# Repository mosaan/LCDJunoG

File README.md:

Roland Juno G LCD Emulator
==========================

LCD replacement project for Roland Juno G.
The original source is [dpeddi's work](https://github.com/dpeddi/LCDJunoG) under BSD-3-Clause license.
```
 * Copyright (c) 2022 Eddi De Pieri
 * Most code borrowed by Pico-DMX by Jostein Løwer 
 * Modified for performance by bjaan
```

Slight modifications as follows
- (WIP) LCD now uses 8-bit parallel mode for better refresh rate.
- Pin definitions in `platformio.ini` now work correctly. See `platformio.ini` for pinout notes.
- Fix few minor bugs.
- Refactor codes for better readability.
- Remove `MODE_BRIGHTNESS` and change functionality of `MODE_BGCOLOR`. (see below)

About `MODE_BGCOLOR`
====================

In `MODE_BGCOLOR`, you can control LCD background color with `LCD CONTRAST` knob on Juno G.

- In the first 3/4 of the knob, a color is selected from the hue ring according to the knob position.
- In the remaining 1/4 of the knob, the background color is fixed at white.

Without `MODE_BGCOLOR`, background color fixed to white.

PlatformIO Build Environments
=============================

There are 2 environments defined:
- `env:pico`: LCD runs in SPI mode.
- `env:pico-parallel`: LCD runs in 8bit parallel mode.

Althogh predefined pin assignments are carefully selected to make PCB creation easier,
you can choose other pins to match your needs.

BOM:
====

- Raspberry Pi Pico
- Display ILI9488 4.0” (purchased from [AliExpress](https://ja.aliexpress.com/item/1005003033844928.html))
- 1.0mm pitch 18-pin flexible flat cable. Length: 210mm (shorter might work), contacts on same side.
- FFC/FPC connector
  - 1.0mm pitch 18-pin, bottom connection; for Juno G connection.
  - (Needed in parallel mode only) 0.5mm pitch 40-pin, top connection; for LCD connection.
- 5 to 10 ohm reistor; for backlight LED on LCD.
- (Optional) 0.1uF ceramic capacitor; for "LCD CONTRAST" knob stability.

Predefined Pin Assignments (Parallel mode):
===========================================

| JunoG Pin | JunoG Function | RpiPico Pin |
| --------- | -------------- | ----------- |
| 18        | +5V            | VSYS        |
| 17        | GND            | GND         |
| 16        | +3V            | (Not used)  |
| 15        | RST            | GP21        |
| 14        | CS2 (*1)       | GP20        |
| 13        | CS1 (*1)       | GP19        |
| 12        | RS             | GP18        |
| 11        | WE             | GP17        |
| 10        | D0             | GP8         |
| 9         | D1             | GP9         |
| 8         | D2             | GP10        |
| 7         | D3             | GP11        |
| 6         | D4             | GP12        |
| 5         | D5             | GP13        |
| 4         | D6             | GP14        |
| 3         | D7             | GP15        |
| 2         | BRGT           | GP28        |
| 1         | BRGT Vref      | +3V         |

*1: Check if the pin configuration might be reversed

| LCD Pin# | LCD Function  | RpiPico Pin         |
| -------- | ------------- | ------------------- |
| 40       | IM2           | GND                 |
| 39       | IM1           | 3.3V                |
| 38       | IM0           | 3.3V                |
| 37       | GND           | GND                 |
| 36       | LED-K         | GND                 |
| 35       | LED-K         | GND                 |
| 34       | LED-K         | GND                 |
| 33       | LED-A         | (3.3V via resistor) |
| 32       | DB15          | (not used)          |
| 31       | DB14          | (not used)          |
| 30       | DB13          | (not used)          |
| 29       | DB12          | (not used)          |
| 28       | DB11          | (not used)          |
| 27       | DB10          | (not used)          |
| 26       | DB9           | (not used)          |
| 25       | DB8           | (not used)          |
| 24       | DB7           | GP7                 |
| 23       | DB6           | GP6                 |
| 22       | DB5           | GP5                 |
| 21       | DB4           | GP4                 |
| 20       | DB3           | GP3                 |
| 19       | DB2           | GP2                 |
| 18       | DB1           | GP1                 |
| 17       | DB0           | GP0                 |
| 16       | GND           | GND                 |
| 15       | RESET         | GP22                |
| 14       | SPI SDO       | (not used)          |
| 13       | SPI SDI/SDA   | (not used)          |
| 12       | RDX           | 3.3V                |
| 11       | WRX/SPI SCL   | GP26                |
| 10       | DCX/RS(SPI-4) | GP27                |
| 9        | CSX/SPI CS    | GND                 |
| 8        | FMARK(TE)     | (not used)          |
| 7        | VDDA          | 3.3V                |
| 6        | VDDI          | 3.3V                |
| 5        | GND           | GND                 |
| 4        | YD            | (not used)          |
| 3        | XR            | (not used)          |
| 2        | YU            | (not used)          |
| 1        | XL            | (not used)          |

Predefined Pin Assignments (SPI mode):
======================================

| JunoG Pin | JunoG Function | RpiPico Pin |
| --------- | -------------- | ----------- |
| 18        | +5V            | VSYS        |
| 17        | GND            | GND         |
| 16        | +3V            | (Not used)  |
| 15        | RST            | GP14        |
| 14        | CS1            | GP12        |
| 13        | CS2            | GP13        |
| 12        | RS             | GP11        |
| 11        | WE             | GP10        |
| 10        | D0             | GP2         |
| 9         | D1             | GP3         |
| 8         | D2             | GP4         |
| 7         | D3             | GP5         |
| 6         | D4             | GP6         |
| 5         | D5             | GP7         |
| 4         | D6             | GP8         |
| 3         | D7             | GP9         |
| 2         | BRGT           | GP26        |
| 1         | BRGT Vref      | +3V         |

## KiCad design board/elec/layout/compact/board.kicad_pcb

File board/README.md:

# Reference board design

This directory contains [atopile](https://atopile.io/) & [KiCad](https://www.kicad.org/) project files for the reference board design.

If you just need PCB gerber files, see `elec/layout/default/production/board.zip`.

## Folder & File structure

- `ato.yaml`: atopile project setting file. see [atopile documentation](https://atopile.io/config/).
- `elec/`: main project files related with atopile and KiCad
  - `footprints/`: KiCad footprints & 3D shape datas.
  - `layout/`: KiCad project files.
  - `src/`: atopile module files.

## To modify & build your own gerber files

1. Modify `elec/src/board.ato` as you like.
2. [Install atopile](https://atopile.io/getting-started/) and run `ato install & ato build` in this folder, then you got netlist file at `build/default.net`.
3. Open `elec/layout/board.kicad_pro` in KiCad and open PCB file (or just open `elec/layout/board.kicad_pcb`).
4. From `File` menu, select `Import -> Netlist...`, then select the generated netlist file.
5. Now netlist updated as you write in `elec/src/board.ato`. Change board layout as you like!

Subsequent steps is the same as the usual board design in KiCad. Refer to  KiCad documentation.

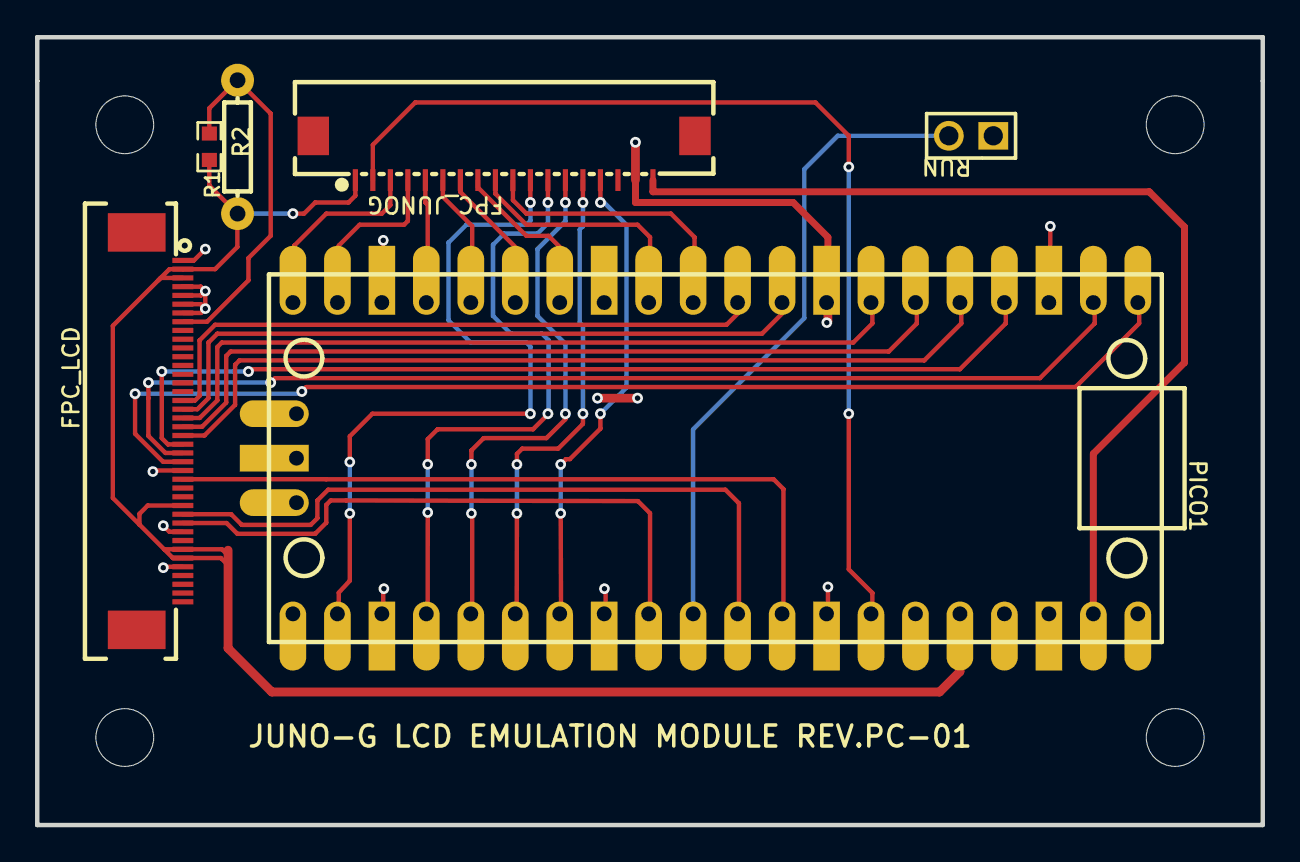
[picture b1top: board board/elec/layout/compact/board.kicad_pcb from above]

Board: 2 copper layers, 70.0 x 45.0 mm, 10 parts (0 on the bottom side), 30 nets.

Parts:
FPC_JUNOG: 1.0K-DX-18PWB; FPC-SMD_18P-P1.00_HDGC_1.0K-DX-18PWB
FPC_LCD: AFC07-S40ECA-00; FPC-SMD_P0.50-40P_LCS-SJ-H2.0
Hole_gge3520: Hole_gge3520
Hole_gge3523: Hole_gge3523
Hole_gge3526: Hole_gge3526
Hole_gge3529: Hole_gge3529
PICO1: RASPBERRY-PI-PICO_TH/SMT (No Debug Pins); RASPBERRY-PI-PICO
R1: 5R1; R0603
R2: 5R1; R_AXIAL-0.3
RUN: HDR-M-2.54_1x2; HDR-M-2.54_1X2

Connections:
3.3V: FPC_JUNOG.1, FPC_LCD.2, FPC_LCD.3, FPC_LCD.29, FPC_LCD.34, FPC_LCD.35, PICO1.36, R1.1, R2.1
+5V: FPC_JUNOG.18, PICO1.39
BGRT: FPC_JUNOG.2, PICO1.34
CS1: FPC_JUNOG.14, PICO1.26
CS2: FPC_JUNOG.13, PICO1.25
D0: FPC_JUNOG.10, PICO1.11
D1: FPC_JUNOG.9, PICO1.12
D2: FPC_JUNOG.8, PICO1.14
D3: FPC_JUNOG.7, PICO1.15
D4: FPC_JUNOG.6, PICO1.16
D5: FPC_JUNOG.5, PICO1.17
D6: FPC_JUNOG.4, PICO1.19
D7: FPC_JUNOG.3, PICO1.20
FPC_LCD_8: FPC_LCD.8, R1.2, R2.2
GND: FPC_JUNOG.17, FPC_LCD.1, FPC_LCD.4, FPC_LCD.5, FPC_LCD.6, FPC_LCD.7, FPC_LCD.25, FPC_LCD.32, FPC_LCD.36, PICO1.3, PICO1.8, PICO1.13, PICO1.18, PICO1.23, PICO1.28, PICO1.33, PICO1.38, RUN.1
LCD_DB0: FPC_LCD.24, PICO1.1
LCD_DB1: FPC_LCD.23, PICO1.2
LCD_DB2: FPC_LCD.22, PICO1.4
LCD_DB3: FPC_LCD.21, PICO1.5
LCD_DB4: FPC_LCD.20, PICO1.6
LCD_DB5: FPC_LCD.19, PICO1.7
LCD_DB6: FPC_LCD.18, PICO1.9
LCD_DB7: FPC_LCD.17, PICO1.10
LCD_DC: FPC_LCD.31, PICO1.29
LCD_RST: FPC_LCD.26, PICO1.32
LCD_WR: FPC_LCD.30, PICO1.31
PICO1_30: PICO1.30, RUN.2
RS: FPC_JUNOG.12, PICO1.24
RST: FPC_JUNOG.15, PICO1.27
WE: FPC_JUNOG.11, PICO1.22

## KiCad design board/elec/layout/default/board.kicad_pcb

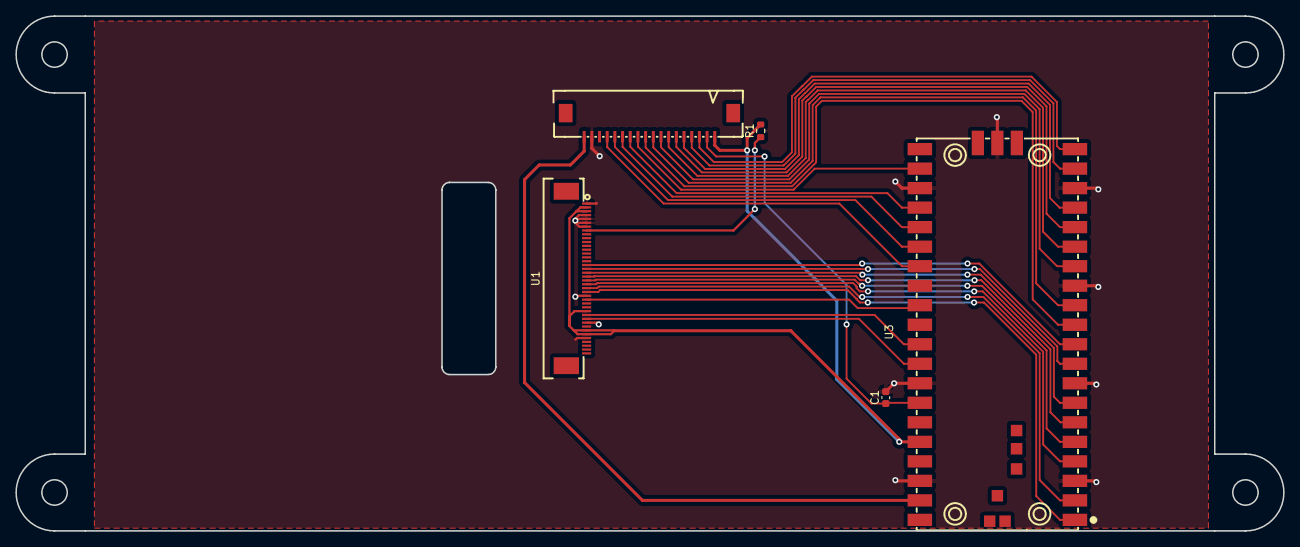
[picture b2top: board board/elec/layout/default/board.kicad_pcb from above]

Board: 2 copper layers, 165.0 x 67.0 mm, 5 parts (0 on the bottom side), 29 nets.

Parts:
C1: 50V 100nF X7R ±10% 0603 Multilayer Ceramic Capaci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; C0603
R1: 100mW Thick Film Resistors 75V ±1% ±400ppm/℃ 10Ω 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; R0603
U1: FPC-SMD_P0.50-40P_LCS-SJ-H2.0
U2: FPC-SMD_AFA01-S18FCC-00
U3: COMM-SMD_L51.0-W21.0-P2.54_SC0916

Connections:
brgt: C1.1, U2.2, U3.34
cs1: U2.13, U3.25
cs2: U2.14, U3.26
d0: U2.10, U3.11
d1: U2.9, U3.12
d2: U2.8, U3.14
d3: U2.7, U3.15
d4: U2.6, U3.16
d5: U2.5, U3.17
d6: U2.4, U3.19
d7: U2.3, U3.20
db0: U1.24, U3.1
db1: U1.23, U3.2
db2: U1.22, U3.4
db3: U1.21, U3.5
db4: U1.20, U3.6
db5: U1.19, U3.7
db6: U1.18, U3.9
db7: U1.17, U3.10
dcx_rs_spi: U1.31, U3.32
gnd: C1.2, U1.1, U1.4, U1.5, U1.6, U1.7, U1.25, U1.32, U1.36, U2.17, U3.3, U3.8, U3.13, U3.18, U3.23, U3.28, U3.33, U3.38, U3.42
led_a: R1.1, U1.8
reset: U1.26, U3.29
rs: U2.12, U3.24
rst: U2.15, U3.27
vdd3: R1.2, U1.2, U1.3, U1.29, U1.34, U1.35, U2.1, U3.36
vdd5: U2.18, U3.39
we: U2.11, U3.22
wrx_spi_scl: U1.30, U3.31

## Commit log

2024-06-02 replace magic numbers to macros and add some comments.
2024-06-02 remove compiler warnings
2024-06-03 bugfix when made renaming
2024-06-03 replace buffer size from 16 to 32 and fetch all pins' state for flexible pin assignment.
2024-06-03 rename [xy]_cs[12] for better readability.
2024-06-03 make example bit expander pio program.
2024-06-04 change Juno-G monitoring pio
2024-06-04 add parallel mode support (not yet tested)
2024-06-05 move constants to header file.
2024-06-05 add experimental debug feature
2024-06-06 add parallel mode pcb garber and corresponding settings.
2024-06-06 refine README
2024-06-06 fix incorrect pin assign
2024-06-06 - better displaying in parallel mode - add #define for "LCD CONTROL" nob functionality
2024-06-06 bugfix: fix incorrect modification of "LCDJunoG.cpp"
2024-06-06 make "prgm_loaded" class member.
2024-06-06 make "prgm_offsets" class member.
2024-06-06 fix incorrect preprocess
2024-06-07 fix pin assign documentation.
2024-06-07 remove MODE_BRIGHTNESS and change MODE_BGCOLOR functionality.
2024-06-07 temp commit
2024-06-08 remove unused variable
2024-06-08 remove tft.startWrite & endWrite on parallel mode.
2024-06-08 fix time counter type for adc.
2024-06-08 define DEBUG_SERIAL mode.
2024-06-08 refactor tft_change_bgcolor.
2024-06-08 minor code formatting.
2024-06-08 add `DEBUG_SERIAL` comment in `platformio.ini`
2024-06-10 add reference PCB file (v1)
2024-06-10 correct 3d model settings.
2024-06-10 replace Pi Pico 3d model
2024-06-10 コンパクト万事知事保存
2024-06-11 replace value with constant.
2024-06-11 fix comment
2024-06-12 remove JUNOG_DEBUGGER feature
2024-06-12 add a resistor in BOM.
2024-06-12 add connection reference image.
2024-06-12 remove test datas
2024-06-12 fix 3d model path of Pi Pico
2024-06-12 add board image.
